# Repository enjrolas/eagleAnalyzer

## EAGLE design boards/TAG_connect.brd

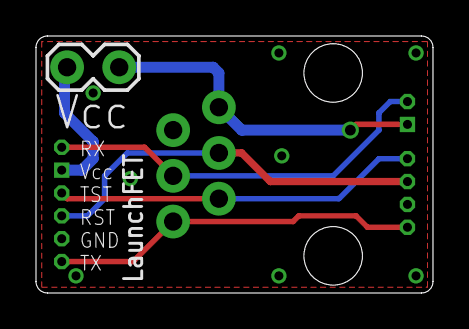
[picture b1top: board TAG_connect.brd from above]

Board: 2 copper layers, 22.1 x 14.3 mm, 4 parts (1 on the bottom side), 7 nets.

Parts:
J2: RJ11-6PTH; RJ11-6
JP2: 1X02_LOCK
U$4: 6-PIN-ICSPEASY-MSP; EASYMSP-6PIN
U$5: 6-PIN-ICSPSAFE-MSP; SAFEMSP-6PIN

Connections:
GND: J2.5, U$4.GND, U$5.GND
RESET: J2.4, U$4.RST, U$5.RST
RX: J2.3, U$4.RX, U$5.RX
TEST: J2.2, U$4.TST, U$5.TST
TX: J2.1, U$4.TX, U$5.TX
VCC_FET: JP2.2, U$4.VCC
VCC_TARGET: J2.6, JP2.1, U$5.VCC

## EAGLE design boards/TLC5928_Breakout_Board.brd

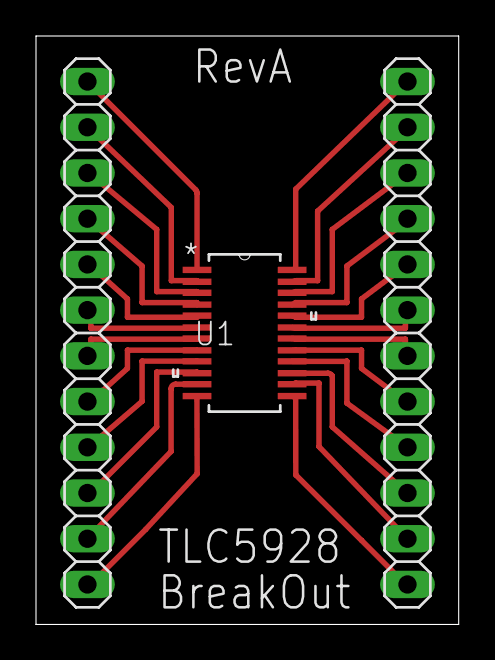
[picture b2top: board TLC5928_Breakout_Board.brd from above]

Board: 2 copper layers, 23.5 x 32.7 mm, 3 parts (0 on the bottom side), 24 nets.

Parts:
JP1, JP2: 1X12
U1: TLC5928_DBQ_24; DBQ24

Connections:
unnamed: JP1.1, U1.24
unnamed: JP1.2, U1.23
unnamed: JP1.3, U1.22
unnamed: JP1.4, U1.21
unnamed: JP1.5, U1.20
unnamed: JP1.6, U1.19
unnamed: JP1.7, U1.18
unnamed: JP1.8, U1.17
unnamed: JP1.9, U1.16
unnamed: JP1.10, U1.15
unnamed: JP1.11, U1.14
unnamed: JP1.12, U1.13
unnamed: JP2.1, U1.12
unnamed: JP2.2, U1.11
unnamed: JP2.3, U1.10
unnamed: JP2.4, U1.9
unnamed: JP2.5, U1.8
unnamed: JP2.6, U1.7
unnamed: JP2.7, U1.6
unnamed: JP2.8, U1.5
unnamed: JP2.9, U1.4
unnamed: JP2.10, U1.3
unnamed: JP2.11, U1.2
unnamed: JP2.12, U1.1

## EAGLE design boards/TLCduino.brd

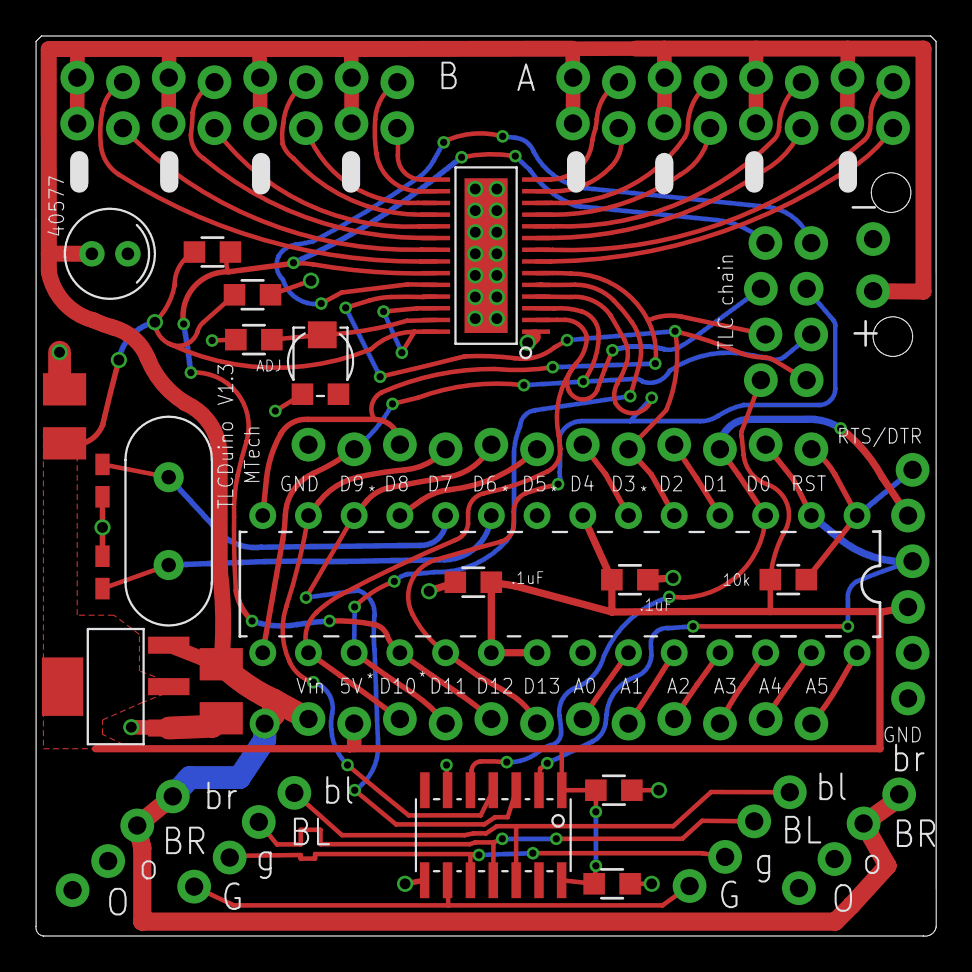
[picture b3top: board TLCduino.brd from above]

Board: 2 copper layers, 50.0 x 50.0 mm, 33 parts (0 on the bottom side), 48 nets.

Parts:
5V: ZLDO1117
C1, C3: 18pF; 0603-CAP
C2, C4, C7, C9: .1uF; 0805
C5, C8: 10uF; 1206
C6: 0.1uF; 0805
C10: 100 uF; 5X11MMCAP
IC1: DIL28-3
JP1: 1X06_LOCK
JP2, JP3, JP6, JP7, JP8, JP9: 1X04_LOCK
JP5: 1X02_LOCK
JPA: 1X08_LOCK
JPB: 1X08_LOCK
JPC: 1X08_LOCK
JPD: 1X08_LOCK
R1: 10k; 0805
R2: 0805
R3: 100k; 0805
U$1: HC49US
U$2, U$5: M12; 1X12_LOCK
U$3: TLC5940; HTSSOP-28
U$4: TRIMPOTTC33X-2; TC33X-2
U$6: MAX13432; SO14

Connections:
5V: 5V.2, 5V.4, C2.2, C4.1, C5.1, C6.1, C7.2, C9.1, IC1.7, IC1.20, IC1.21, JP1.4, JP3.1, R1.1, R3.2, U$3.26, U$3.28, U$5.11, U$6.1, U$6.14
A: JP6.4, JP8.1, U$6.12
A0: IC1.23, U$5.6
A1: IC1.24, U$5.5
A2: IC1.25, U$5.4
A3: IC1.26, U$5.3
A4: IC1.27, U$5.2
A5: IC1.28, U$5.1
B: JP6.3, JP8.2, U$6.11
D0: IC1.2, JP1.3, U$2.2, U$6.2
D1: IC1.3, JP1.2, U$2.3, U$6.5
D2: IC1.4, U$2.4
D3: IC1.5, JP2.1, U$2.5, U$3.25
D4: IC1.6, U$2.6
D5: IC1.11, U$2.7
D6: IC1.12, U$2.8, U$6.3
D7: IC1.13, U$2.9, U$6.4
D8: IC1.14, JP3.2, U$2.10, U$3.6
D9: IC1.15, JP2.2, U$2.11, U$3.3
D10: IC1.16, JP3.3, U$3.2, U$5.10
D11: IC1.17, U$3.5, U$5.9
D12: IC1.18, JP3.4, R3.1, U$3.23, U$5.8
D13: IC1.19, JP2.3, U$3.4, U$5.7
GND: 5V.1, C1.1, C2.1, C3.1, C4.2, C5.2, C6.2, C7.1, C8.2, C9.2, C10.-, IC1.8, IC1.22, JP1.5, JP1.6, JP5.2, JP7.3, JP7.4, JP9.1, JP9.2, R2.2, U$2.12, U$3.1, U$3.PAD, U$4.1, U$6.6, U$6.8
IREF: R2.1, U$3.27, U$4.2
unnamed: C3.2, IC1.10, U$1.2
unnamed: C1.2, IC1.9, U$1.1
OUT0A: JPB.1, U$3.7
OUT1A: JPA.8, U$3.8
OUT2A: JPB.3, U$3.9
OUT3A: JPA.6, U$3.10
OUT4A: JPB.5, U$3.11
OUT5A: JPA.4, U$3.12
OUT6A: JPB.7, U$3.13
OUT7A: JPA.2, U$3.14
OUT8A: JPD.1, U$3.15
OUT9A: JPC.8, U$3.16
OUT10A: JPD.3, U$3.17
OUT11A: JPC.6, U$3.18
OUT12A: JPD.5, U$3.19
OUT13A: JPC.4, U$3.20
OUT14A: JPD.7, U$3.21
OUT15A: JPC.2, U$3.22
RESET: IC1.1, JP1.1, R1.2, U$2.1
SOUT: JP2.4, U$3.24
VIN: 5V.3, C8.1, C10.+, JP5.1, JP7.1, JP7.2, JP9.3, JP9.4, JPA.1, JPA.3, JPA.5, JPA.7, JPB.2, JPB.4, JPB.6, JPB.8, JPC.1, JPC.3, JPC.5, JPC.7, JPD.2, JPD.4, JPD.6, JPD.8, U$5.12
Y: JP6.1, JP8.4, U$6.9
Z: JP6.2, JP8.3, U$6.10

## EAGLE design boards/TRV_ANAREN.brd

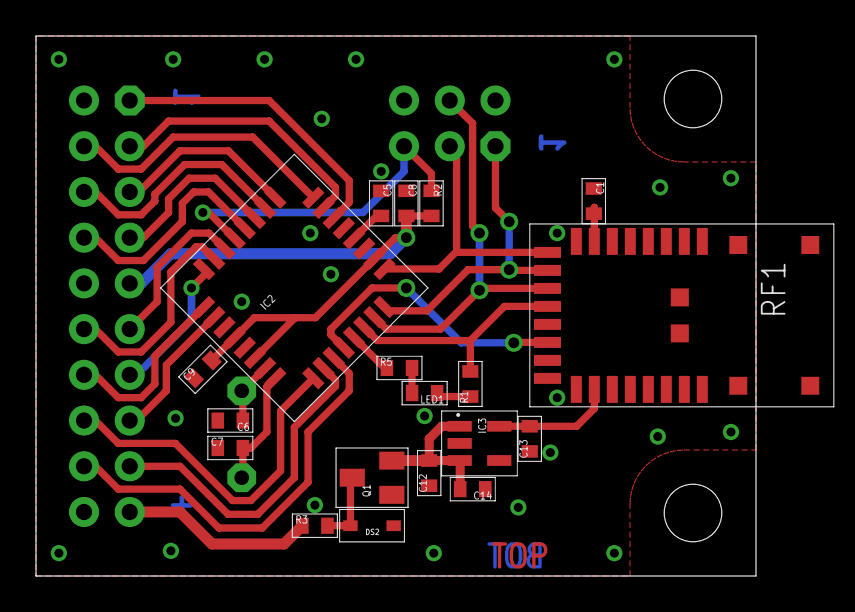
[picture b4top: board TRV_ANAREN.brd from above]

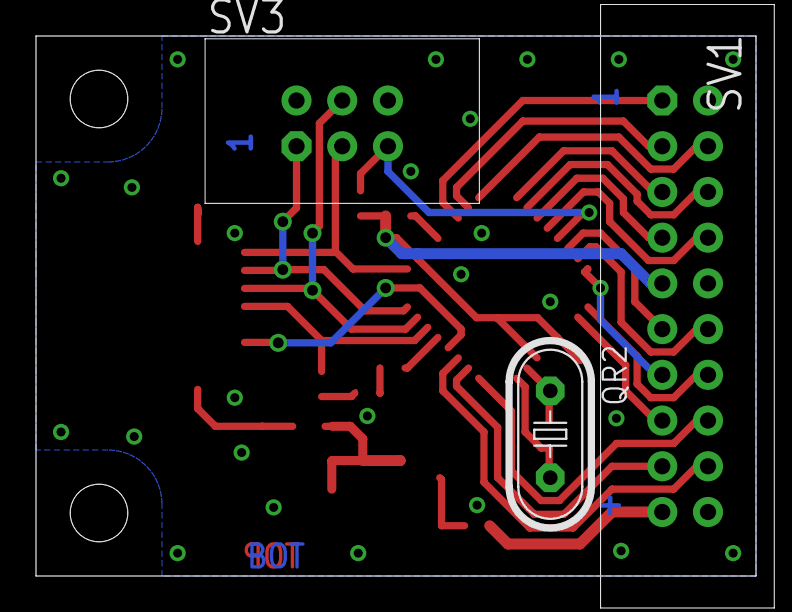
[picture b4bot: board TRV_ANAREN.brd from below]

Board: 2 copper layers, 40.0 x 30.0 mm, 22 parts (3 on the bottom side), 32 nets.

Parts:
C1: n.b.; 0603
C5, C8, C9, C14: 100n; 0603
C6, C7: 22p; 0603
C12, C13: 1u; 0603
DS2: PESD12VL1BA; SOD323
IC2: MEGA168PA-AU; TQFP32-08
IC3: LP2992-IM5-3.3; SOT23-5
LED1: LEDR; 0603
Q1: IRLM9301; SOT23
QR2: 16.000; HC49U-V
R1, R2: 10k; 0603
R3: 0R; 0603
R5: 330R; 0603
RF1: ANAREN
SV1: ISP; ML20
SV3: ISP; ML6

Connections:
+3V3: C8.2, C9.2, C13.2, IC2.4, IC2.6, IC2.18, IC3.5, LED1.1, R1.1, R2.2, RF1.18, SV1.9, SV3.2
GND: C1.1, C5.1, C6.2, C7.1, C8.1, C9.1, C12.1, C13.1, C14.1, DS2.C, IC2.3, IC2.5, IC2.21, IC3.2, Q1.1, RF1.8, RF1.17, SV1.10, SV1.20, SV3.6
LED: IC2.13, R5.1
MISO: IC2.16, RF1.10, SV3.1
MOSI: IC2.15, RF1.11, SV3.4
unnamed: C1.2, RF1.7
unnamed: IC2.22, SV1.1
unnamed: DS2.A, Q1.3, R3.2
unnamed: C5.2, IC2.20
unnamed: C12.2, C14.2, IC3.1, IC3.3, Q1.2
unnamed: C6.1, IC2.7, QR2.1
unnamed: C7.2, IC2.8, QR2.2
unnamed: LED1.2, R5.2
unnamed: R3.1, SV1.19
PC0: IC2.23, SV1.3
PC1: IC2.24, SV1.4
PC2: IC2.25, SV1.5
PC3: IC2.26, SV1.6
PC4: IC2.27, SV1.7
PC5: IC2.28, SV1.8
PD2: IC2.32, SV1.13
PD3: IC2.1, SV1.14
PD4: IC2.2, SV1.15
PD5: IC2.9, SV1.16
PD6: IC2.10, SV1.17
PD7: IC2.11, SV1.18
RIRQ: IC2.12, RF1.14
RSEL: IC2.14, R1.2, RF1.12
RST: IC2.29, R2.1, SV3.5
RXD: IC2.30, SV1.11
SCK: IC2.17, RF1.9, SV3.3
TXD: IC2.31, SV1.12

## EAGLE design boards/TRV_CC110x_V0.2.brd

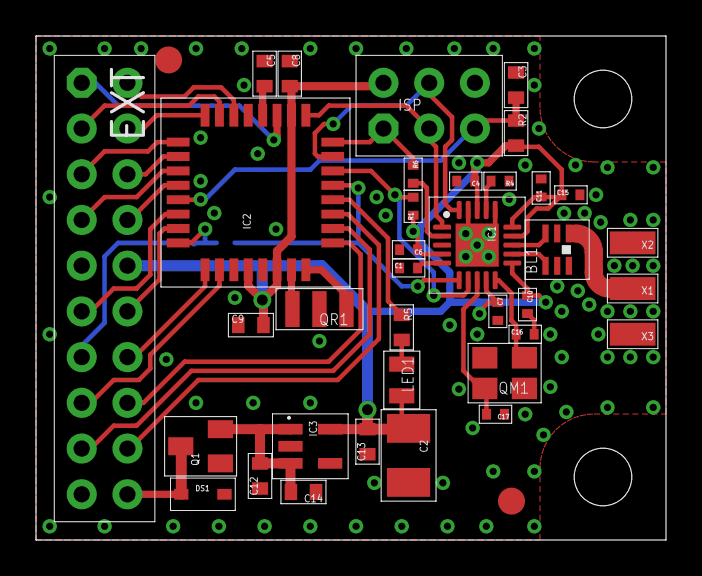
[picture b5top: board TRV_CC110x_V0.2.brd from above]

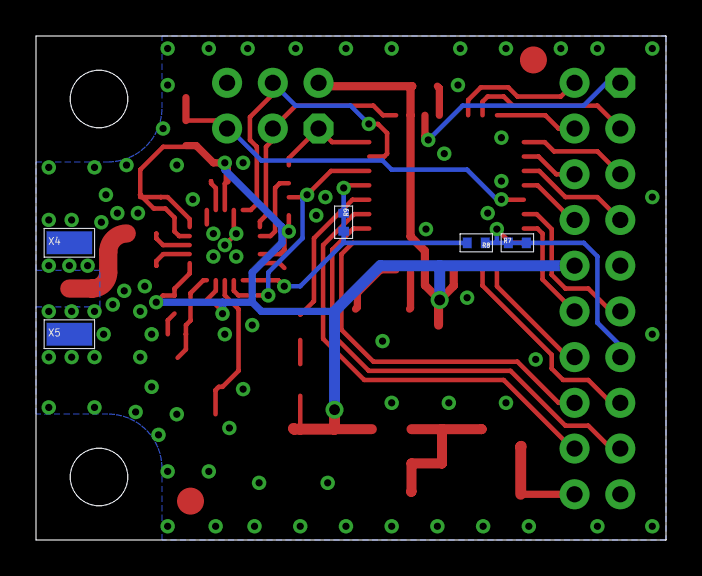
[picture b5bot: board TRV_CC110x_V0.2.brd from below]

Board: 2 copper layers, 35.0 x 28.0 mm, 43 parts (5 on the bottom side), 39 nets.

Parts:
BL1: BL
C1, C6: 100n; 0402
C2: 10u; SMC_B
C3, C5, C8, C9, C14: 100n; 0603
C4, C11: 220p; 0402
C7, C15: 10n; 0402
C10: 2p2; 0402
C12, C13: 1u; 0603
C16, C17: 27p; 0402
DS1: PESD12VL1BA; SOD323
EXT: EXT; ML20S
IC1: VQFN20
IC2: MEGA328P-AU; TQFP32-08
IC3: LP2992-IM5-3.3; SOT23-5
ISP: ISP; ML6S
LED1: LEDR; 0805
Q1: IRLML9301; SOT23
QM1: 26M; SMD_4P_3.2X2.5
QR1: 8M; CR
R1: 10k; 0402
R2: 10k; 0603
R4: 56k; 0402
R5: 330R; 0603
R6: 330R; 0402
R7, R8, R9: 0402
U$1, U$2: FUICIDAL1.5
X1: ANT; S2.54/1.27
X2, X3, X4, X5: GND; S2.54/1.27

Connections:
+3V3: C2.+, C4.1, C6.1, C7.1, C8.2, C9.2, C10.1, C11.1, C13.2, C15.1, EXT.10, IC1.-4, IC1.-9, IC1.-11, IC1.-14, IC1.-15, IC1.-18, IC2.4, IC2.6, IC2.18, IC3.5, ISP.2, LED1.C, R1.1, R2.2
GND: BL1.2, BL1.5, BL1.6, C1.1, C2.-, C3.1, C4.2, C5.1, C6.2, C7.2, C8.1, C9.1, C10.2, C11.2, C12.1, C13.1, C14.1, C15.2, C16.2, C17.1, DS1.A, EXT.9, EXT.19, IC1.-16, IC1.-19, IC1.P, IC2.3, IC2.5, IC2.21, IC3.2, ISP.6, Q1.1, QM1.2, QM1.4, QR1.M, R4.1, X2.1, X3.1, X4.1, X5.1
MISO: IC2.16, ISP.1, R6.1
MOSI: IC1.-20, IC2.15, ISP.4
unnamed: C1.2, IC1.-5
unnamed: IC1.-17, R4.2
unnamed: EXT.2, IC2.22
unnamed: IC1.-2, R6.2
unnamed: DS1.C, EXT.20, Q1.3
unnamed: C5.2, IC2.20
unnamed: IC2.8, QR1.1
unnamed: IC2.7, QR1.2
unnamed: IC2.12, R5.1
unnamed: EXT.13, IC2.32, R7.1, R7.2, R8.1
unnamed: C12.2, C14.2, IC3.1, IC3.3, Q1.2
unnamed: BL1.3, IC1.-13
unnamed: BL1.4, IC1.-12
unnamed: EXT.1, IC2.19
unnamed: BL1.1, X1.1
unnamed: C17.2, IC1.-8, QM1.3
unnamed: C16.1, IC1.-10, QM1.1
unnamed: LED1.A, R5.2
PC0: EXT.3, IC2.23
PC1: EXT.4, IC2.24
PC2: EXT.5, IC2.25
PC3: EXT.6, IC2.26
PC4: EXT.7, IC2.27
PC5: EXT.8, IC2.28
PD3: EXT.14, IC2.1
PD4: EXT.15, IC2.2
PD5: EXT.16, IC2.9
PD6: EXT.17, IC2.10
PD7: EXT.18, IC2.11
RIRQ: IC1.-6, IC2.13, R8.2, R9.1, R9.2
RSEL: IC1.-7, IC2.14, R1.2
RST: C3.2, IC2.29, ISP.5, R2.1
RXD: EXT.11, IC2.30
SCK: IC1.-1, IC2.17, ISP.3
TXD: EXT.12, IC2.31

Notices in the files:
parts and their libraries:
SparkFun-Connectors: Licensing: CC v3.0 Share-Alike You are welcome to use this library for commercial purposes.
